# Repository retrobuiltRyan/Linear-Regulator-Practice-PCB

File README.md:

# Linear-Regulator-Practice-PCB
Beginner 2-layer PCB project with kiCAD. This board contains three 78xx linear regulators. 

Schematic:

PCB Layout and render.

BoM
| Reference         | Qty | Value                    | Footprint                                                    | DigiKey P/N      |
|-------------------|-----|--------------------------|--------------------------------------------------------------|------------------|
| C1,C3,C5          | 3   | 0.22uF 50V CER           | Capacitor_SMD:C_1206_3216Metric                              | 445-2283-1-ND    |
| C2,C4,C6          | 3   | 0.1uF 50V                | Capacitor_SMD:C_1206_3216Metric                              | 1276-1068-1-ND   |
| D4                | 1   | D                        | Diode_SMD:D_SMC_Handsoldering                                | S5AC-FDICT-ND    |
| J1,J2,J4,J5       | 4   | Screw_Terminal_2_P3.50mm | TerminalBlock_Phoenix_PT-1,5-2-3.5-H_1x02_P3.50mm_Horizontal | 732-2747-ND      |
| R1,R2,R3,R4,R5,R6 | 6   | 330                      | Resistor_SMD:R_1206_3216Metric                               | 311-330FRCT-ND   |
| U1                | 1   | L7805                    | Package_TO_SOT_SMD:TO-252-2                                  | 497-7255-1-ND    |
| U2                | 1   | L7809                    | Package_TO_SOT_SMD:TO-252-2                                  | BA7809FP-E2CT-ND |
| U5                | 1   | L7812                    | Package_TO_SOT_SMD:TO-263-3_TabPin2                          | 296-44522-1-ND   |

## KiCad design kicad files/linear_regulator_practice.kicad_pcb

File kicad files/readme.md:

1) download each file (raw). 
2) place in a folder of the same name. 
3) open with kiCAD version 10.0+

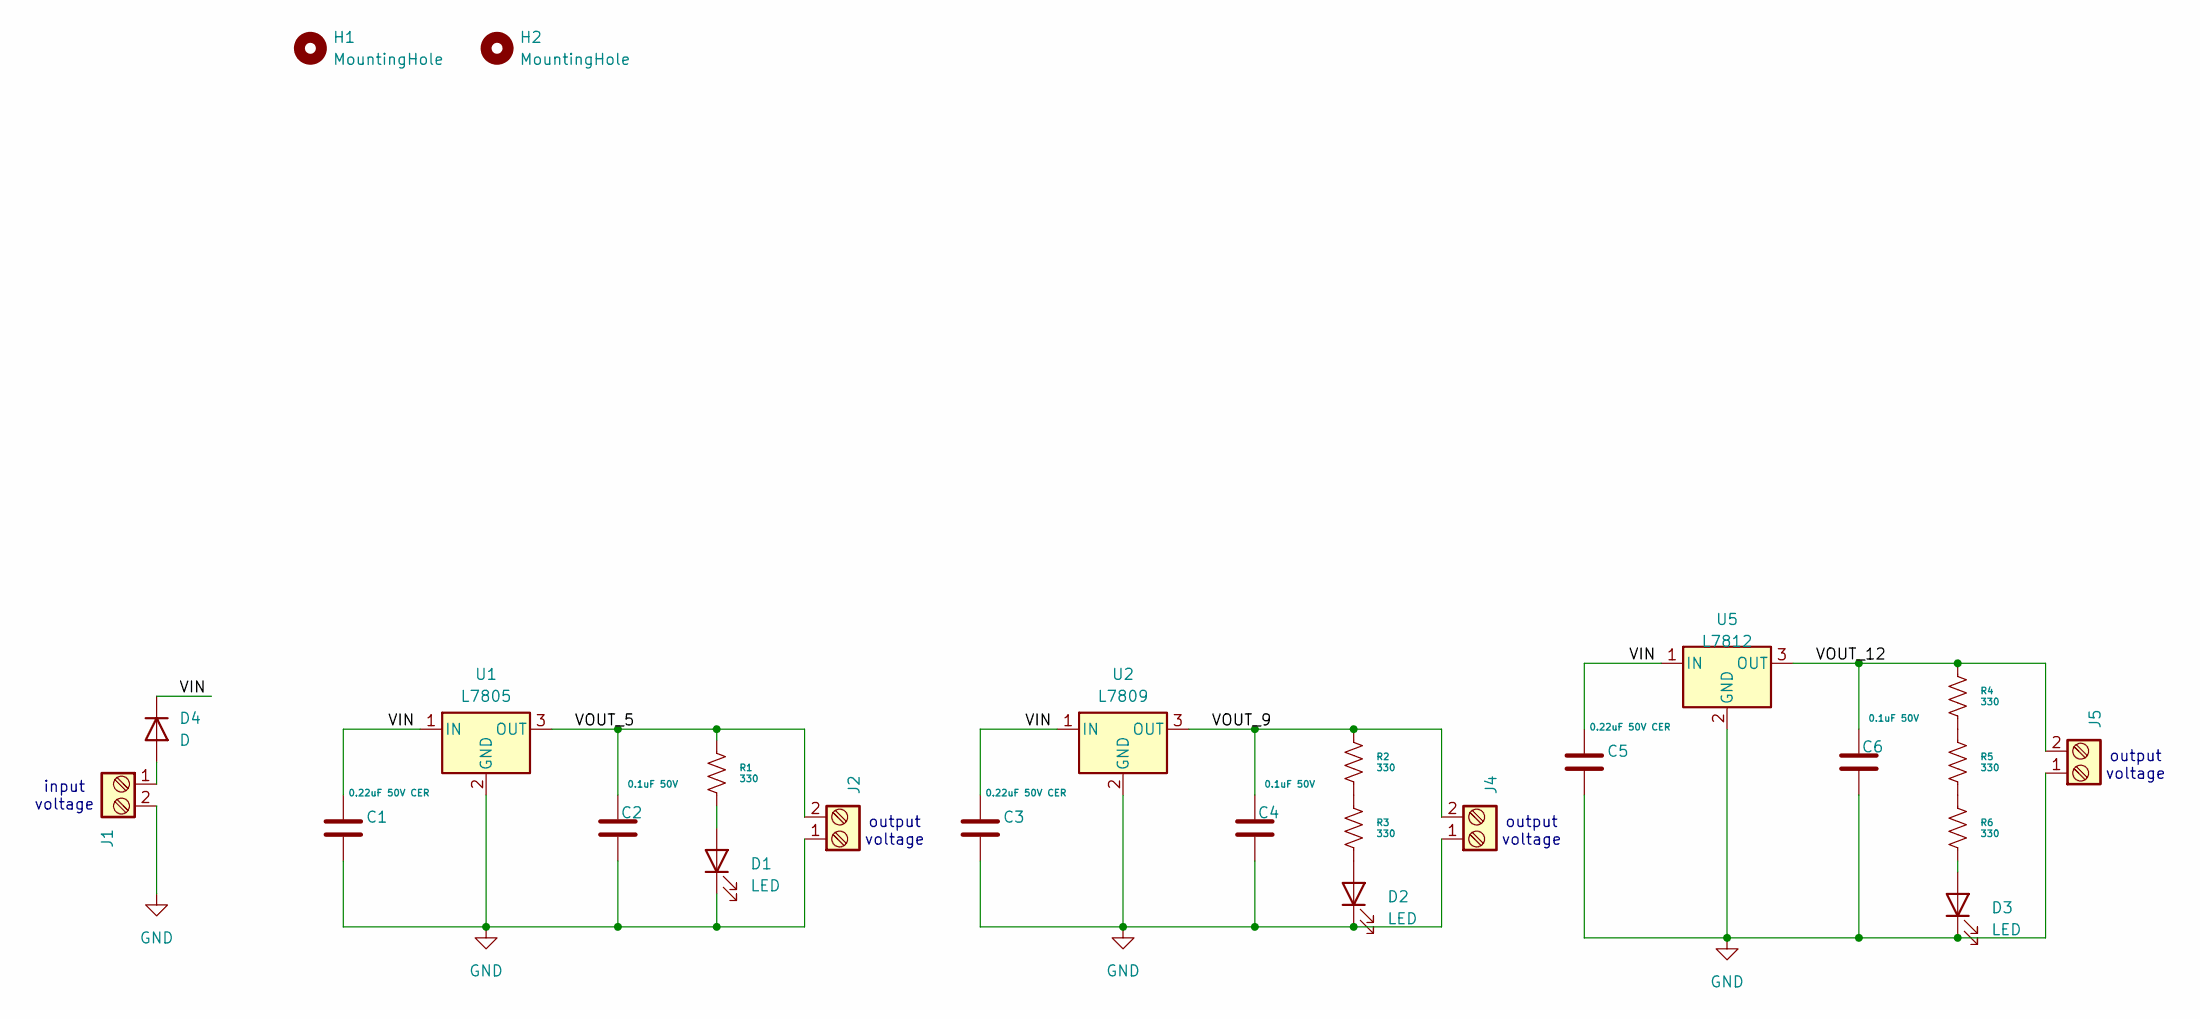
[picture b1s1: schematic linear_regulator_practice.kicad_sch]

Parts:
C1, C3, C5: 0.22uF 50V CER; C_1206_3216Metric; DigiKey P/N 445-2283-1-ND
C2, C4, C6: 0.1uF 50V; C_1206_3216Metric; DigiKey P/N 1276-1068-1-ND
D1, D2, D3: LED; LED_1206_3216Metric; DigiKey P/N 1080-1419-1-ND
D4: D; D_SMC_Handsoldering; DigiKey P/N S5AC-FDICT-ND
H1, H2: MountingHole; MountingHole_3.2mm_M3_DIN965_Pad
J1, J2, J4, J5: Screw_Terminal_2_P3.50mm; TerminalBlock_Phoenix_PT-1,5-2-3.5-H_1x02_P3.50mm_Horizontal; DigiKey P/N 732-2747-ND
R1, R2, R3, R4, R5, R6: 330; R_1206_3216Metric; DigiKey P/N 311-330FRCT-ND
U1: L7805; TO-252-2; DigiKey P/N 497-7255-1-ND
U2: L7809; TO-252-2; DigiKey P/N BA7809FP-E2CT-ND
U5: L7812; TO-263-3_TabPin2; DigiKey P/N 296-44522-1-ND

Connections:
/VIN: C1.1, C3.1, C5.1, D4.1 (K), U1.1 (IN), U2.1 (IN), U5.1 (IN)
/VOUT_5: C2.1, J2.2, R1.1, U1.3 (OUT)
/VOUT_9: C4.1, J4.2, R2.1, U2.3 (OUT)
/VOUT_12: C6.1, J5.2, R4.1, U5.3 (OUT)
GND: C1.2, C2.2, C3.2, C4.2, C5.2, C6.2, D1.1 (K), D2.1 (K), D3.1 (K), J1.2, J2.1, J4.1, J5.1, U1.2 (GND), U2.2 (GND), U5.2 (GND)
unnamed: D1.2 (A), R1.2
unnamed: D2.2 (A), R3.2
unnamed: D3.2 (A), R6.2
unnamed: D4.2 (A), J1.1
unnamed: R2.2, R3.1
unnamed: R4.2, R5.1
unnamed: R5.2, R6.1

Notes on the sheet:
output voltage
input voltage

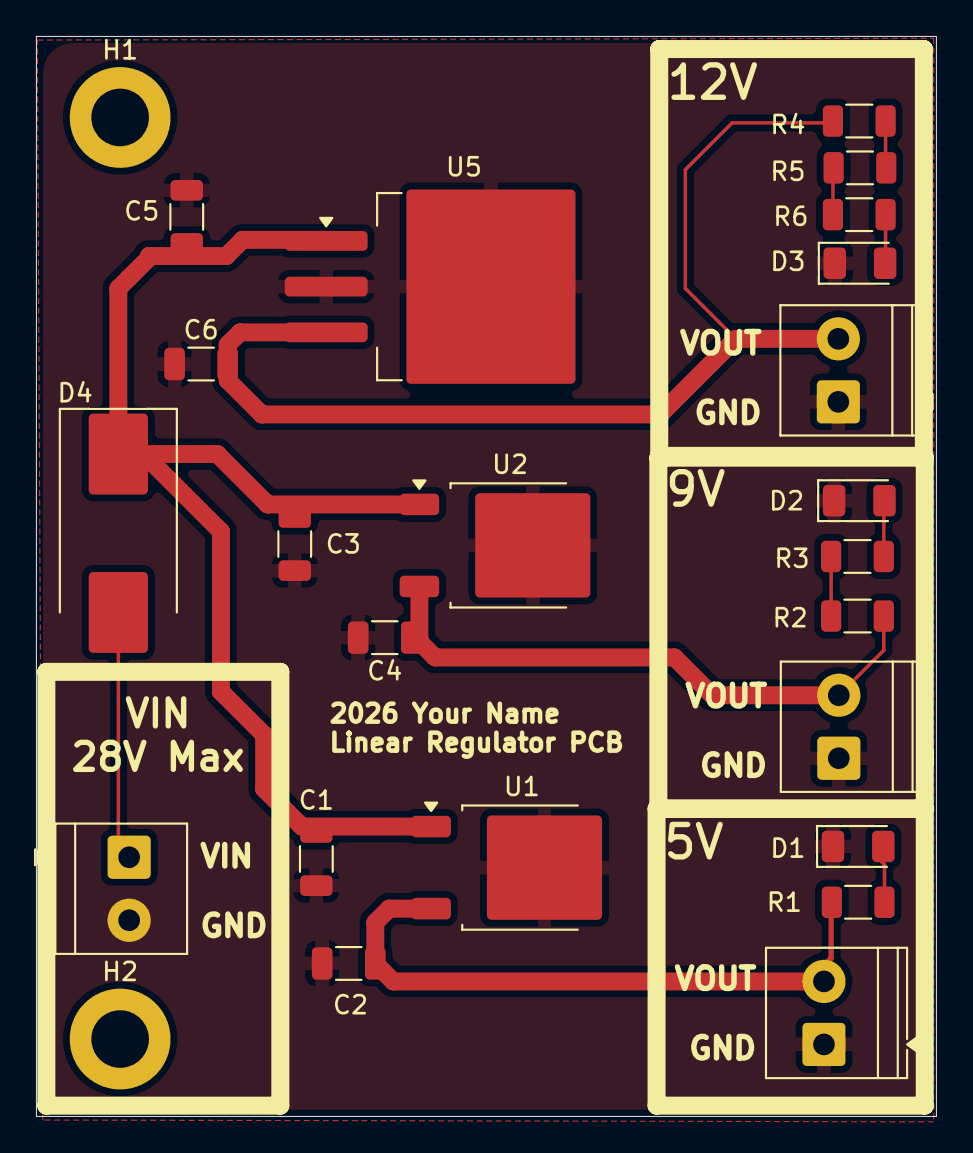
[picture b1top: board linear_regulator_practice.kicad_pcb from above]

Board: 2 copper layers, 50.0 x 60.0 mm, 25 parts (0 on the bottom side), 12 nets.
